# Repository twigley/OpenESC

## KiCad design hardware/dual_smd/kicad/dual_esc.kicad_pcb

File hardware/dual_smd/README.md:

# Dual-motor SMD ESC, AM32 version

Two independent 3-phase BLDC channels on one small board. Each channel has
its own Artery AT32F421 running the stock **AM32** firmware target
**`RR_ROBOT_DUAL_ESC_F421`** (hardware groups `AT_C` + `AT_045`), a TI
DRV8300 gate driver and three AOS AON7934 dual half-bridge MOSFETs. A shared
buck gives 5 V for the receiver (BEC), and an LDO gives 3.3 V for both MCUs.

**Status:** schematic drawn and checked (ERC clean). The PCB is **placed
but not routed**: 6 layers, 31 x 20 mm. It needs interactive routing in
KiCad (see [Routing notes](#routing-notes)). Not built. Part numbers marked
"verify" must be checked before ordering.

## Targets

| Item | Value |
|---|---|
| Battery | 2S Li-ion, 6.0 to 8.4 V |
| Current | about 10-12 A per motor, limit set in AM32 |
| Firmware | AM32, stock target `RR_ROBOT_DUAL_ESC_F421`, flashed on both MCUs; no `USE_INVERTED_*` |
| Board | 31 x 20 mm, 6-layer trial (L2 GND, L3/L4 signal, L5 VBAT), parts on both sides |
| Bulk caps | 4 x 220 uF 16 V on the battery leads (off-board, in the BOM) |

## Pin map (both channels, from AM32 `Inc/targets.h`)

| Function | AT32F421 pin (QFN32 no.) | Connects to |
|---|---|---|
| Phase A high / low | PA10 TMR1_CH3 (20) / PB1 TMR1_CH3N (15) | DRV8300 INHA (22) / INLA (1) |
| Phase B high / low | PA9 TMR1_CH2 (19) / PB0 TMR1_CH2N (14) | INHB (23) / INLB (2) |
| Phase C high / low | PA8 TMR1_CH1 (18) / PA7 TMR1_CH1N (13) | INHC (24) / INLC (3) |
| BEMF A / B / C | PA0 (6) / PA4 (10) / PA5 (11), comparator inverting inputs | 10k / 4.7k dividers from each phase |
| Neutral | PA1 (7), comparator non-inverting input | 3 x 10k from the phases, 1.5k to GND |
| Signal in | PA2 TMR15_CH1 (8) | 100 R to the SIG pad |
| Telemetry | PB6 USART1_TX (29) | TLM pad |
| Battery voltage | PA3 ADC3 (9) | 100k / 10k divider (shared by both MCUs) |
| Current | PA6 ADC6 (12) | INA186A1 via 1k / 10 nF |
| SWD | PA13 (23) / PA14 (24), NRST (4) | SWDIO / SWCLK / NRST pads, plus shared 3V3 / GND pads |
| BOOT0 | pin 31 | 10k to GND |

The pins were checked against the AT32F421 datasheet v2.02, Figure 4. The
AT32F421 QFN32 is **not** pin-identical to the STM32F051K8U: its pins 16 and
32 are PB2 and PB8, not VSS. Ground is the exposed pad only.

## Circuit notes

- **Gate driver:** DRV8300DRGER (VQFN-24), the D variant with internal
  bootstrap diodes. MODE is left open, so GLx follows INLx (non-inverted). DT
  is left open for the fixed 200 ns dead time, on top of AM32's DEAD_TIME 50.
  GVDD runs straight from VBAT (5-20 V) with 10 uF + 100 nF. Bootstrap caps
  are 100 nF 25 V. Source: TI SLVSFG5D Table 6-1 and section 9.2.2.
- **MOSFETs:** AON7934 has the high-side FET Q1 (D1 = VBAT) and the low-side
  FET Q2 (S2 = low-side source node) in one 3 x 3 mm package. The switch
  node is pad 9 (S1/D2). The footprint is made from AOS drawing PO-00136 rev
  C (DFN3x3A_8L_EP2) and is in `kicad/OpenESC_dual.pretty`. There are no
  gate series resistors, to save space. Each low-side gate has a 10k
  pull-down to GND. GND is the source potential plus the shunt's few mV.
- **Current sense:** each channel has one 0.5 mOhm low-side shunt from the
  three low-side sources to GND, feeding an INA186A1 (25 V/V). That gives
  12.5 mV/A against AM32's MILLIVOLT_PER_AMP 12, so readings are about 4 %
  high, trimmable in the configurator. REF is tied to GND (unidirectional).
- **BEMF:** 10k / 4.7k dividers (ratio 0.32, so 8.4 V gives 2.7 V). The
  virtual neutral is 3 x 10k with 1.5k to GND, the same ratio. There are no
  filter caps. The AM32 repository has firmware only, so there were no AM32
  reference values to compare against.
- **5 V BEC:** TPS62933 (3.8-30 V in, 3 A) at 1.2 MHz (RT to GND), with
  2.2 uH and 2 x 22 uF. The feedback divider is 31.6k / 10k for 5.0 V
  (TI SLUSEA4D Table 10-2). At 6.0 V in, the needed duty cycle is about 85 %,
  within the 98 % maximum.
- **3.3 V:** TLV75533PDBV from 5 V, with 1 uF in and out.
- **Heat:** RDS(on) at 4.5 V is 11.6-15.8 mOhm max per FET, and a 2S pack
  gives only 6-8 V of gate drive. At 12 A that is about 1.7-2.3 W in the
  conducting pair. Expect airflow to be needed above about 8 A continuous.

## Flashing AM32

1. With the battery disconnected, power the board from a 3.3 V SWD
   programmer through the 3V3 / GND pads. Connect SWDIO, SWCLK and NRST for
   the channel being flashed. Flash the AM32 bootloader built for the F421
   with its input on PA2 (from the AM32 bootloader releases; check the file
   name there) using an SWD probe that supports the AT32F421, such as
   Artery's AT-Link or an ST-Link with OpenOCD's AT32 support. Repeat for
   the second MCU.
2. Connect the battery and the signal wires. With the AM32 configurator
   (web or desktop), through a betaflight passthrough or a USB-serial
   one-wire adapter on each SIG pad, flash `RR_ROBOT_DUAL_ESC_F421` to each
   channel and set the current limit (10-12 A), motor direction and timing.
3. After that, firmware updates go over the signal wire. SWD is needed
   only once.

## PCB status

**Placed, not routed.** The board is 31 x 20 mm with 6 layers. All 129
on-board parts fit with no courtyard overlaps, and placement DRC is clean
(only unconnected items). Renders: `kicad/render_top.png`,
`kicad/render_bottom.png`.

### Stackup (1.6 mm, JLC 6-layer style)

| Layer | Use |
|---|---|
| L1 top (1 oz) | MOSFETs, phase / battery pads, shunts, gate resistors, BEC, LDO; power zones (phase nodes, low-side source buses, VBAT drain islands) |
| L2 | Solid GND plane |
| L3, L4 | Signal |
| L5 | VBAT plane (GND beyond x = 27.4 mm) |
| L6 bottom (1 oz) | Both DRV8300s, both MCUs, current-sense amps, BEMF networks, small passives |

**Outer copper is 1 oz.** JLC offers 2 oz outer on 6-layer boards, but then
the minimum trace / space is 0.16 mm, and the QFN escapes need 0.13 mm.
At 1 oz the outer power zones carry about half the current of 2 oz, so the
10-12 A phase and battery paths should be widened where possible,
solder-tinned, or reinforced with bus wire. The MOSFET drains also reach the
L5 VBAT plane through vias.

**Via-in-pad:** every DRV8300 and MCU signal pin has a filled via-in-pad,
0.3 mm diameter with a 0.15 mm hole, epoxy filled and capped. That is within
JLC's multilayer minimum of a 0.15 mm hole / 0.25 mm via, at a surcharge.
One JLC blog gives 0.20 mm as the minimum hole for via-in-pad, so confirm
before ordering. A 0.20 mm hole means 0.35-0.4 mm vias, which do not fit
side by side at the MCU's 0.4 mm pitch. The vias are staggered along the
pad length.

**Placement:**
- Both DRV8300s are in the bottom middle band, with only the low-side bus
  zones above them. Bootstrap caps sit between the drivers, GVDD caps beside
  them.
- The 4.7 R gate series resistors are on top, just under each gate pin.
- The BEMF networks, BEMF filter caps and gate pull-downs are on the bottom,
  under the phase pads.
- The MCUs are bottom right with nothing above their pins (checked with
  `tools/above_check.py`).
- The bus caps are under the phase pads. The LDO, BEC and SWD pads are top
  right.

**0201 parts:** 48 small-signal parts are 0201. LCSC stock was checked
2026-11-21:
- 100 nF 10 V: C284966
- 10 nF 25 V: C285010
- 1 nF 50 V: C301887
- 10k: C6853700
- Other resistor values: UNI-ROYAL 0201WMF ±1 % series

### Routing notes

Automated routing was tried and plateaued at about 55-65 conflicting nets
in every setup: Freerouting 2.5.0, and `tools/gridroute.py` / `negroute.py`
on 4 and 6 layers, with and without via-in-pad. Route it interactively in
KiCad:

1. Route the DRV8300 and MCU fanouts first. Drop each signal pin through
   its via-in-pad to L3 / L4, then run the six INH/INL lines per channel,
   the gate lines (driver -> 4.7 R on top -> FET gate) and the BST / SH
   lines on L3 / L4.
2. Keep each GHx / SHx pair together. Keep gate loops short.
3. Power stays in the L1 / L6 zones: phase nodes, low-side buses to the
   shunts, and VBAT drain islands with their vias to L5. Don't route
   signals through them on L1.
4. Run the BEMF / neutral / ISENSE lines to the MCU on L3 / L4. The shunt
   Kelvin lead (INA186 IN+) goes from the LS tap via.
5. Finish with the top / bottom GND fill and stitching vias to L2. GND /
   VBAT pads already have fanout vias where `tools/route_pcb.py` placed
   them.

## Files

- `tools/gen_schematic.py`: the netlist (`PARTS`), the single source of
  truth. Running it writes `BOM.csv` and redraws the schematic.
- `tools/draw_schematic.py`: draws `kicad/dual_esc.kicad_sch` as a wired,
  readable sheet. Labels are used only between blocks.
- `tools/check_schematic.py`: rebuilds connectivity from the drawn wires and
  fails unless it matches `PARTS`.
- `tools/above_check.py`: checks no part on the other side sits over a DRV8300 / MCU pin.
- `tools/negroute.py`: negotiated-congestion (rip-up) router experiment.
- `tools/gridroute.py`: grid maze router for the outer layers (power fanout, then signal nets).
- `tools/route_pcb.py`: power fanout, Freerouting run, keep-out removal, GND fill and stitching.
- `tools/build_pcb.py`: builds `kicad/dual_esc.kicad_pcb`. It places the parts,
  draws the power copper as zones, and links each footprint to its schematic
  symbol so the GUI's Update PCB keeps working. Run it with KiCad's Python.

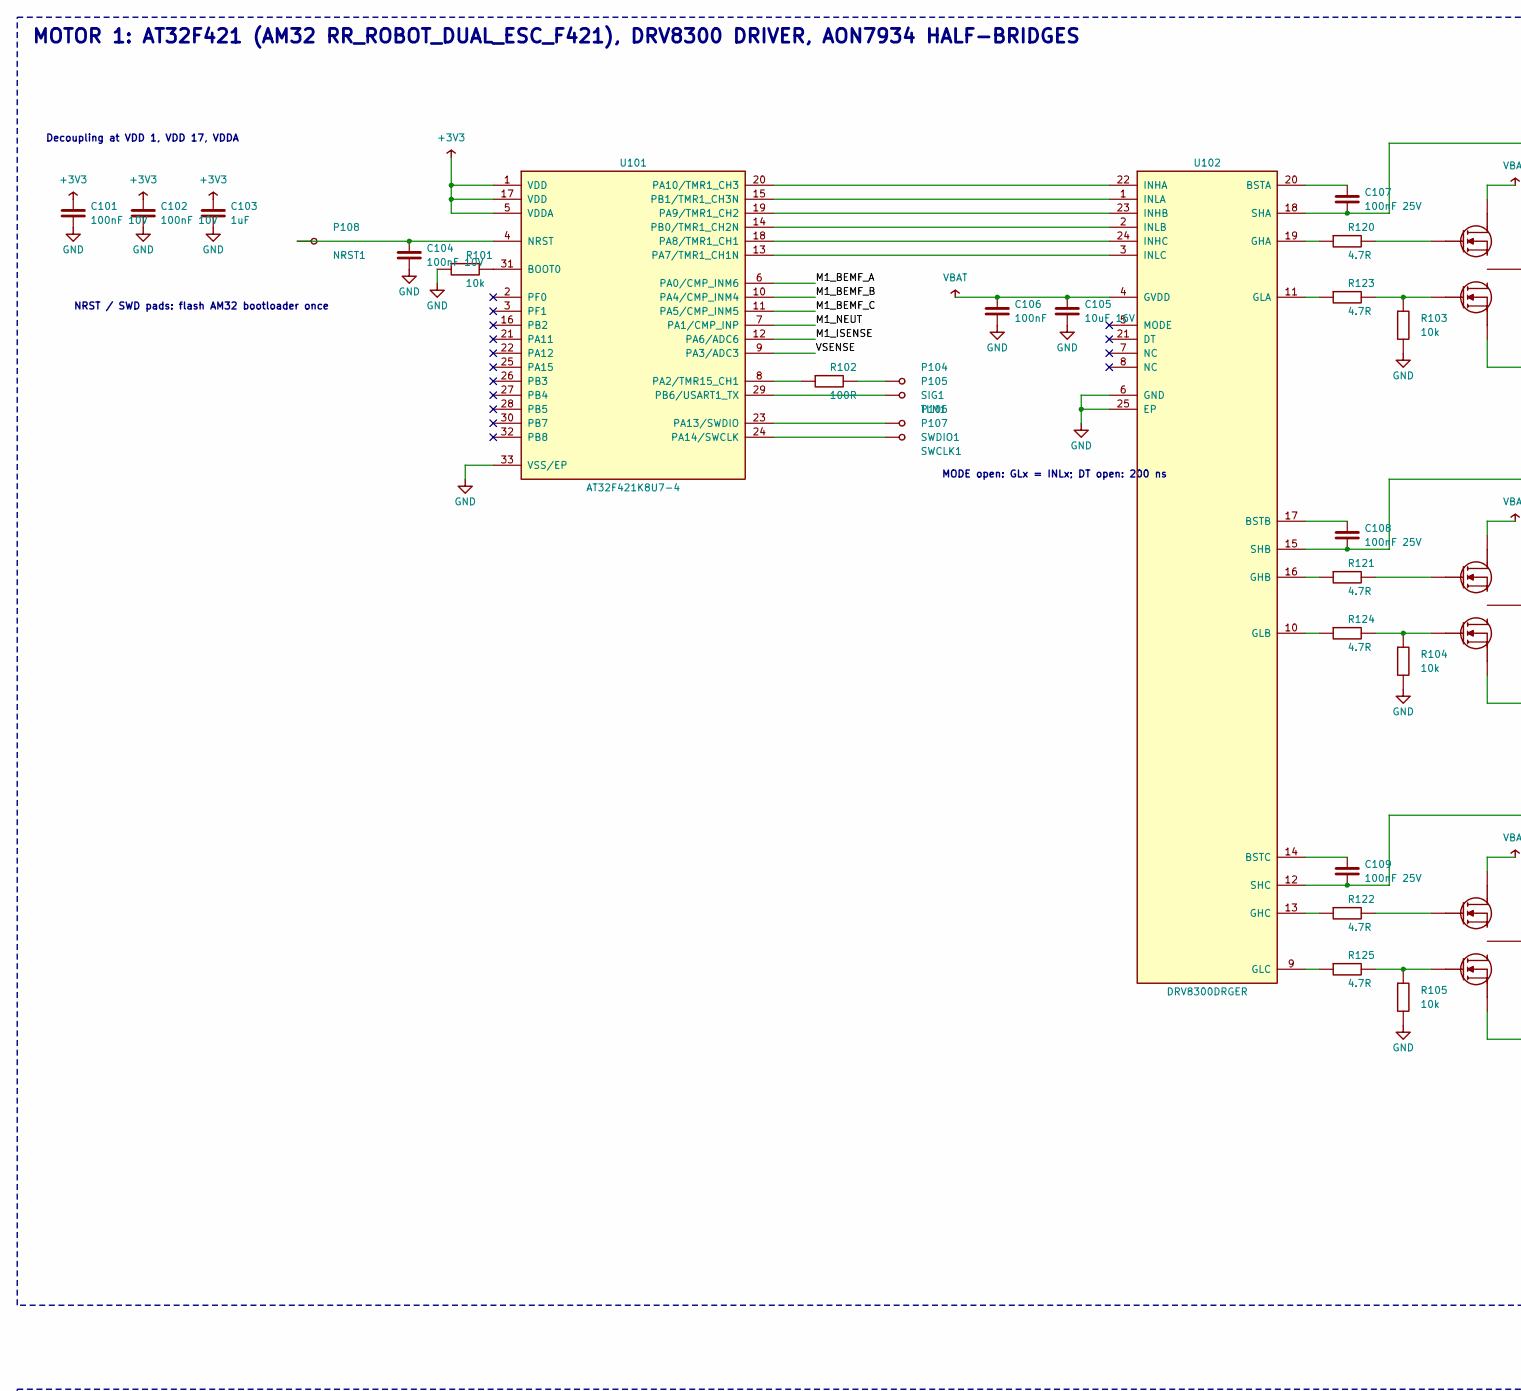
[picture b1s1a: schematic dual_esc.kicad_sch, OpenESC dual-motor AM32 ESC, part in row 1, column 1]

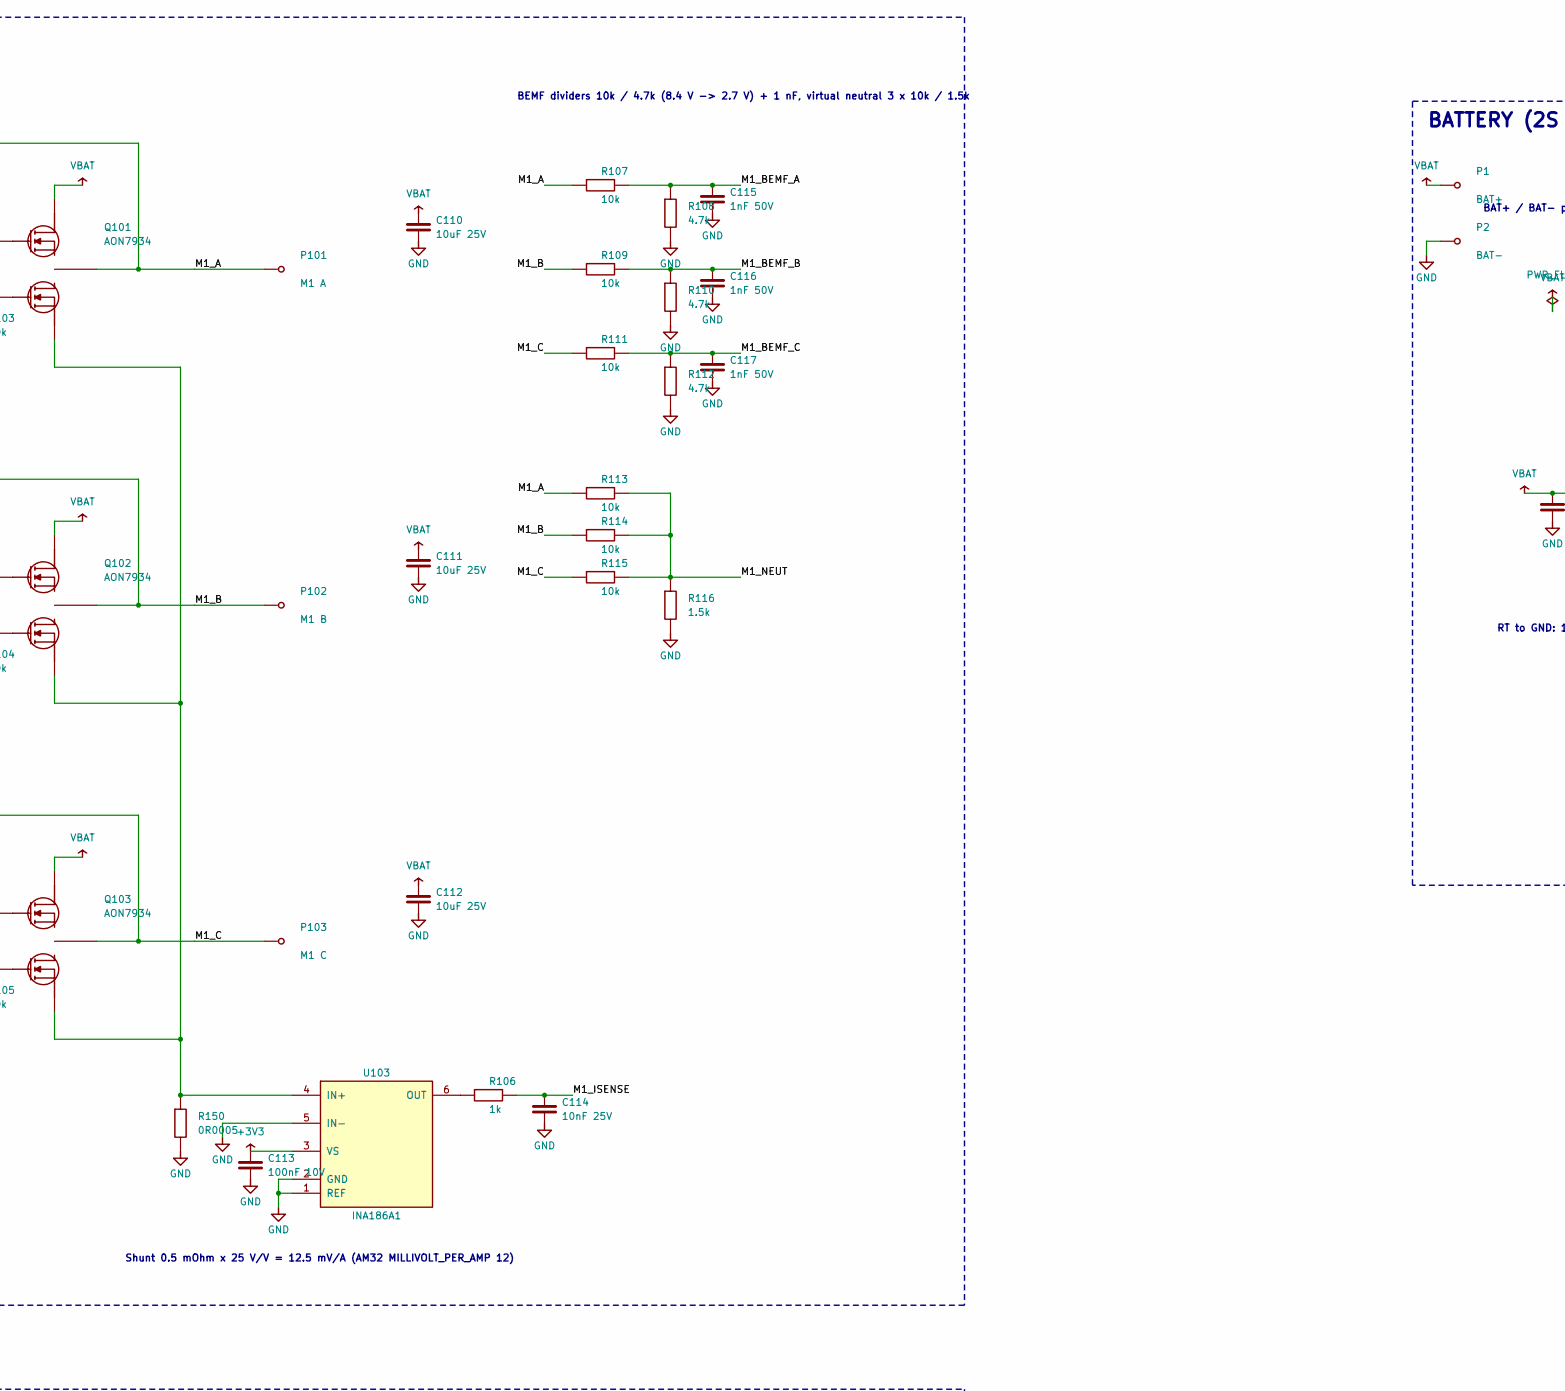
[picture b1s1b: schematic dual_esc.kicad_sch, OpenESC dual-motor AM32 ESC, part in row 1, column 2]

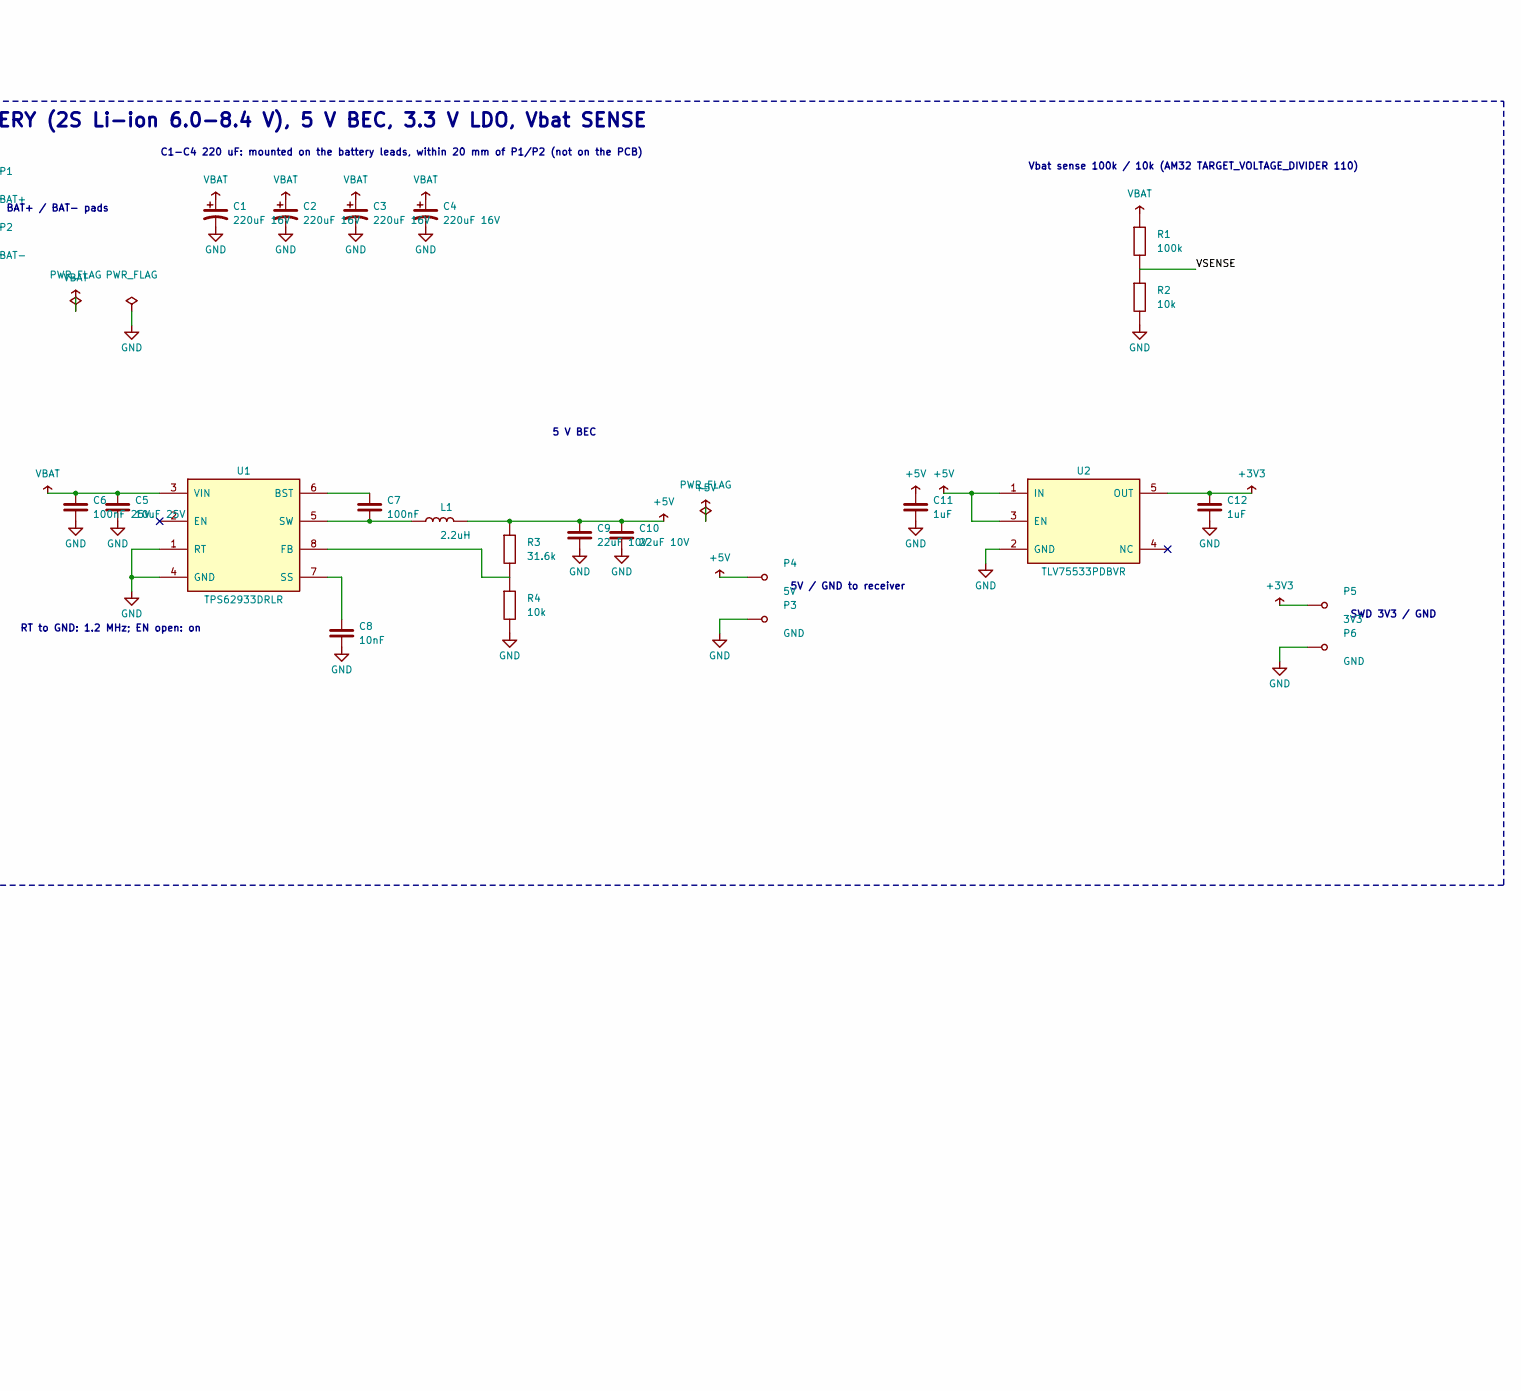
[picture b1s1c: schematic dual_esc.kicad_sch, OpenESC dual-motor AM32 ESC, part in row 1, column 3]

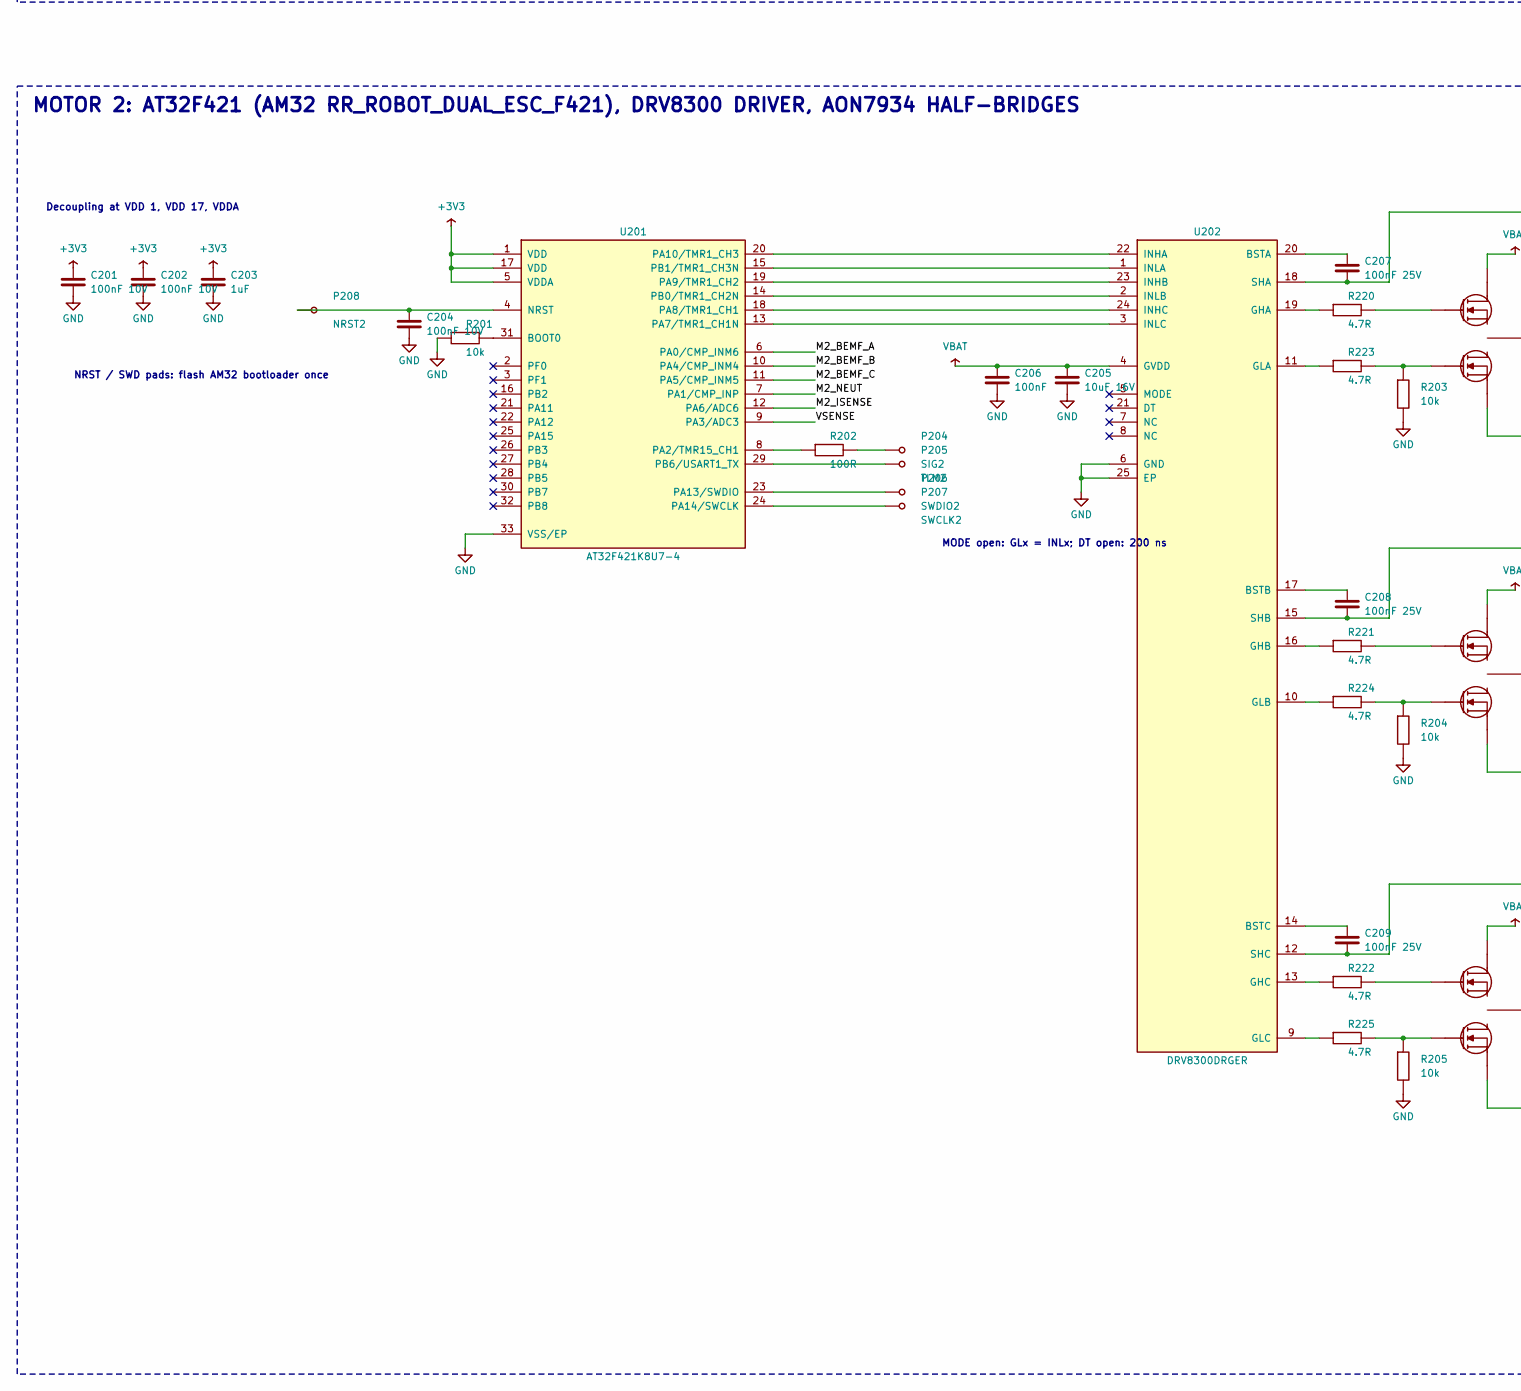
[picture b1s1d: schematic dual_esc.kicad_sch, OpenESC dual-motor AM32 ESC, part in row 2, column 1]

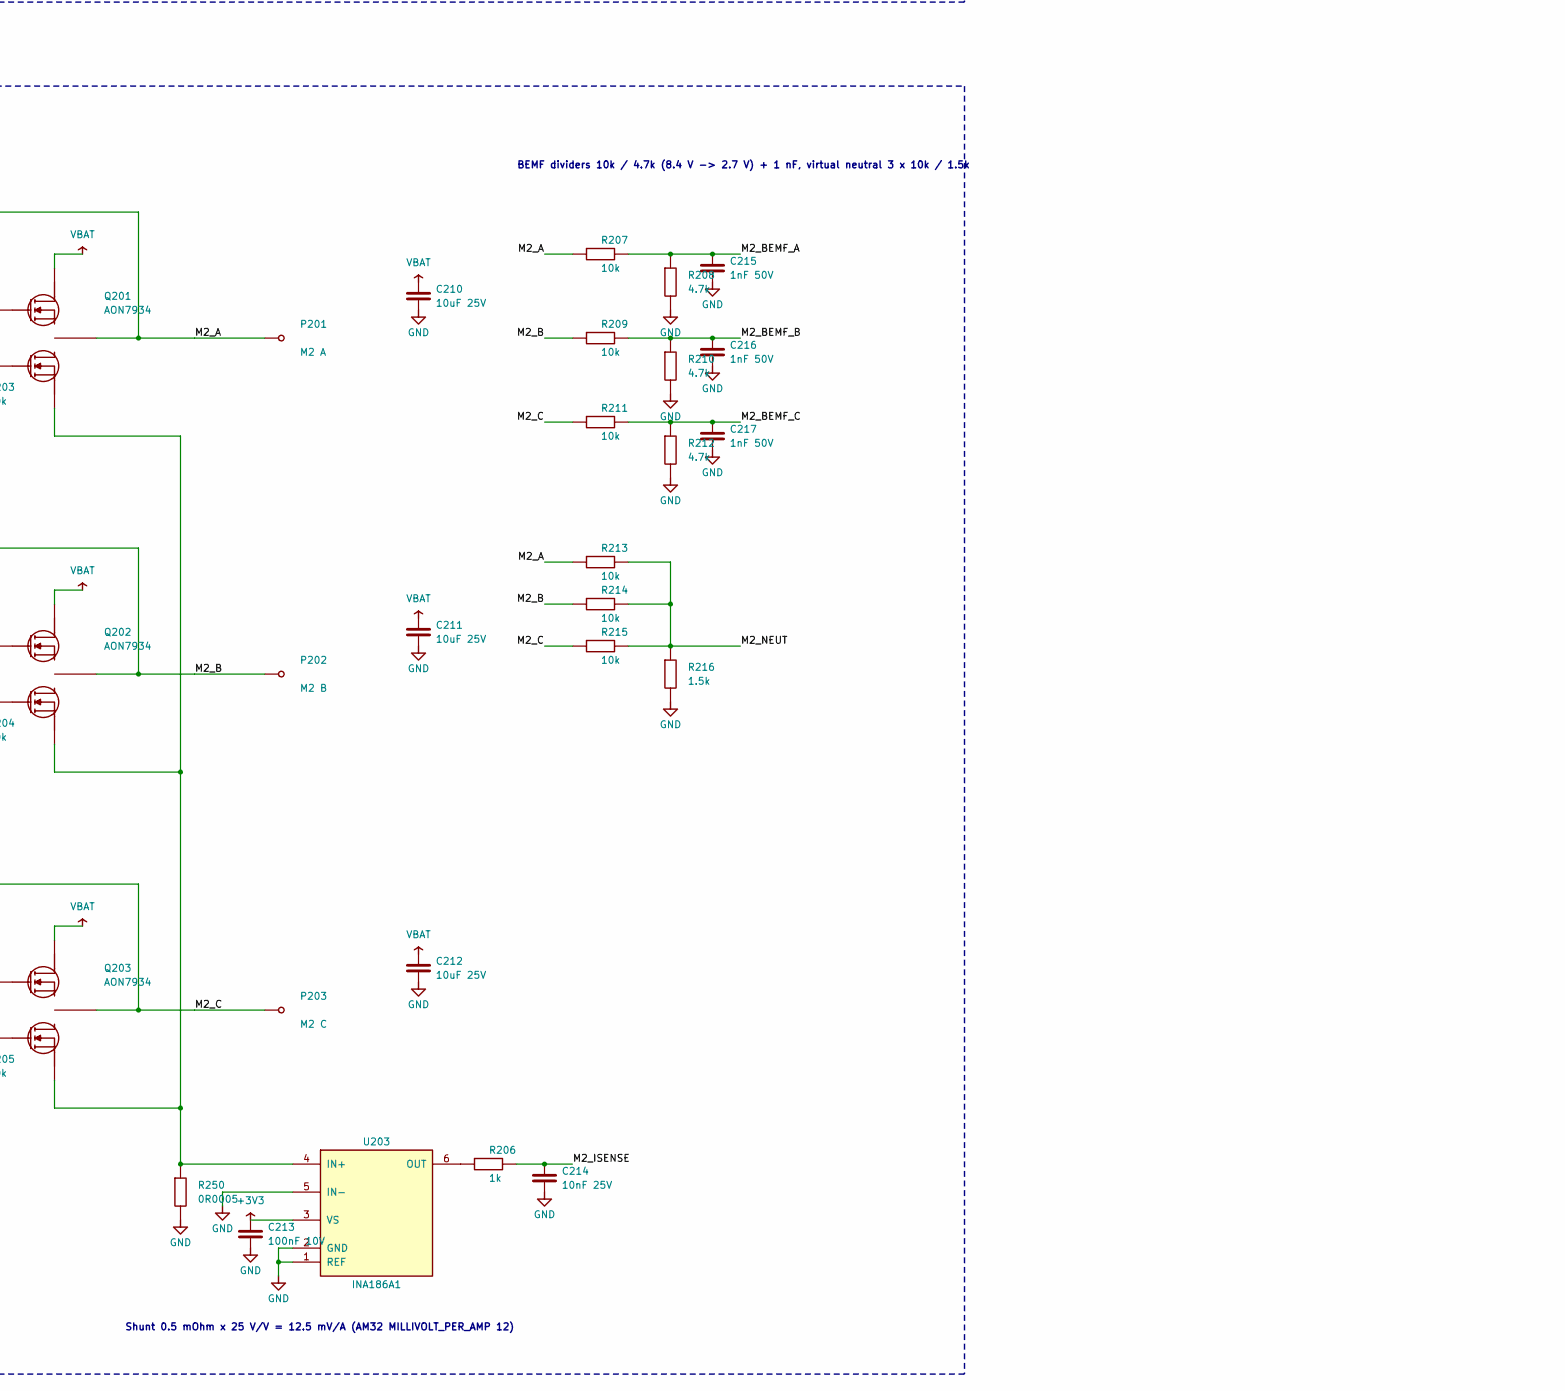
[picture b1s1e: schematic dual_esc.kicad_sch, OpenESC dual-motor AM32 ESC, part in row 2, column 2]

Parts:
C1, C2, C3, C4: 220uF 16V; CP_Elec_6.3x7.7; MPN low-ESR polymer/electrolytic, on batter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
C5, C110, C111, C112, C210, C211, C212: 10uF 25V; C_0805_2012Metric
C6, C107, C108, C109, C207, C208, C209: 100nF 25V; C_0402_1005Metric
C7, C106, C206: 100nF; C_0402_1005Metric
C8: 10nF; C_0402_1005Metric
C9, C10: 22uF 10V; C_0603_1608Metric
C11, C12, C103, C203: 1uF; C_0402_1005Metric
C101, C102, C104, C113, C201, C202, C204, C213: 100nF 10V; C_0201_0603Metric
C105, C205: 10uF 16V; C_0603_1608Metric
C114, C214: 10nF 25V; C_0201_0603Metric
C115, C116, C117, C215, C216, C217: 1nF 50V; C_0201_0603Metric
L1: 2.2uH; L_Changjiang_FNR3015S; MPN Changjiang FNR3015S2R2MT, 3x3 mm (verif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
P1: BAT+; Pad_SMD_2.5x5.0mm
P2: BAT-; Pad_SMD_2.5x5.0mm
P3: GND; Pad_SMD_1.5x1.5mm_Tight
P4: 5V; Pad_SMD_1.5x1.5mm_Tight
P5: 3V3; Pad_SMD_1.0x1.0mm_Tight
P6: GND; Pad_SMD_1.0x1.0mm_Tight
P101: M1 A; Pad_SMD_2.5x3.0mm
P102: M1 B; Pad_SMD_2.5x3.0mm
P103: M1 C; Pad_SMD_2.5x3.0mm
P104: SIG1; Pad_SMD_1.5x1.5mm_Tight
P105: TLM1; Pad_SMD_1.0x1.0mm_Tight
P106: SWDIO1; Pad_SMD_1.0x1.0mm_Tight
P107: SWCLK1; Pad_SMD_1.0x1.0mm_Tight
P108: NRST1; Pad_SMD_1.0x1.0mm_Tight
P201: M2 A; Pad_SMD_2.5x3.0mm
P202: M2 B; Pad_SMD_2.5x3.0mm
P203: M2 C; Pad_SMD_2.5x3.0mm
P204: SIG2; Pad_SMD_1.5x1.5mm_Tight
P205: TLM2; Pad_SMD_1.0x1.0mm_Tight
P206: SWDIO2; Pad_SMD_1.0x1.0mm_Tight
P207: SWCLK2; Pad_SMD_1.0x1.0mm_Tight
P208: NRST2; Pad_SMD_1.0x1.0mm_Tight
Q101, Q102, Q103, Q201, Q202, Q203: AON7934; AOS_DFN3x3A-8L-EP2_3x3mm_P0.65mm; MPN AON7934
R1: 100k; R_0201_0603Metric
R2, R101, R103, R104, R105, R107, R109, R111, R113, R114, R115, R201, R203, R204, R205, R207, R209, R211, R213, R214, R215: 10k; R_0201_0603Metric
R3: 31.6k; R_0402_1005Metric
R4: 10k; R_0402_1005Metric
R102, R202: 100R; R_0201_0603Metric
R106, R206: 1k; R_0201_0603Metric
R108, R110, R112, R208, R210, R212: 4.7k; R_0201_0603Metric
R116, R216: 1.5k; R_0201_0603Metric
R120, R121, R122, R123, R124, R125, R220, R221, R222, R223, R224, R225: 4.7R; R_0201_0603Metric
R150, R250: 0R0005; R_1206_3216Metric; MPN e.g. WSLP1206R0005 (verify)
U1: TPS62933DRLR; SOT-583-8; MPN TPS62933DRLR
U2: TLV75533PDBVR; SOT-23-5; MPN TLV75533PDBVR
U101, U201: AT32F421K8U7-4; QFN-32-1EP_4x4mm_P0.4mm_EP2.65x2.65mm; MPN AT32F421K8U7-4
U102, U202: DRV8300DRGER; VQFN-24-1EP_4x4mm_P0.5mm_EP2.45x2.45mm; MPN DRV8300DRGER
U103, U203: INA186A1; SOT-363_SC-70-6; MPN INA186A1IDCKR

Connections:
+3V3: C12.1, C101.1, C102.1, C103.1, C113.1, C201.1, C202.1, C203.1, C213.1, P5.1, U2.5 (OUT), U101.1 (VDD), U101.5 (VDDA), U101.17 (VDD), U103.3 (VS), U201.1 (VDD), U201.5 (VDDA), U201.17 (VDD), U203.3 (VS)
+5V: C9.1, C10.1, C11.1, L1.2, P4.1, R3.1, U2.1 (IN), U2.3 (EN)
BEC_BST: C7.1, U1.6 (BST)
BEC_FB: R3.2, R4.1, U1.8 (FB)
BEC_SS: C8.1, U1.7 (SS)
BEC_SW: C7.2, L1.1, U1.5 (SW)
GND: C1.2, C2.2, C3.2, C4.2, C5.2, C6.2, C8.2, C9.2, C10.2, C11.2, C12.2, C101.2, C102.2, C103.2, C104.2, C105.2, C106.2, C110.2, C111.2, C112.2, C113.2, C114.2, C115.2, C116.2, C117.2, C201.2, C202.2, C203.2, C204.2, C205.2, C206.2, C210.2, C211.2, C212.2, C213.2, C214.2, C215.2, C216.2, C217.2, P2.1, P3.1, P6.1, R2.2, R4.2, R101.1, R103.2, R104.2, R105.2, R108.2, R110.2, R112.2, R116.2, R150.2, R201.1, R203.2, R204.2, R205.2, R208.2, R210.2, R212.2, R216.2, R250.2, U1.1 (RT), U1.4 (GND), U2.2 (GND), U101.33 (VSS/EP), U102.6 (GND), U102.25 (EP), U103.1 (REF), U103.2 (GND), U103.5 (IN-), U201.33 (VSS/EP), U202.6 (GND), U202.25 (EP), U203.1 (REF), U203.2 (GND), U203.5 (IN-)
M1_A: C107.2, P101.1, Q101.9 (S1/D2), R107.1, R113.1, U102.18 (SHA)
M1_B: C108.2, P102.1, Q102.9 (S1/D2), R109.1, R114.1, U102.15 (SHB)
M1_BEMF_A: C115.1, R107.2, R108.1, U101.6 (PA0/CMP_INM6)
M1_BEMF_B: C116.1, R109.2, R110.1, U101.10 (PA4/CMP_INM4)
M1_BEMF_C: C117.1, R111.2, R112.1, U101.11 (PA5/CMP_INM5)
M1_BOOT0: R101.2, U101.31 (BOOT0)
M1_BSTA: C107.1, U102.20 (BSTA)
M1_BSTB: C108.1, U102.17 (BSTB)
M1_BSTC: C109.1, U102.14 (BSTC)
M1_C: C109.2, P103.1, Q103.9 (S1/D2), R111.1, R115.1, U102.12 (SHC)
M1_GHA: Q101.1 (G1), R120.2
M1_GHA_D: R120.1, U102.19 (GHA)
M1_GHB: Q102.1 (G1), R121.2
M1_GHB_D: R121.1, U102.16 (GHB)
M1_GHC: Q103.1 (G1), R122.2
M1_GHC_D: R122.1, U102.13 (GHC)
M1_GLA: Q101.8 (G2), R103.1, R123.2
M1_GLA_D: R123.1, U102.11 (GLA)
M1_GLB: Q102.8 (G2), R104.1, R124.2
M1_GLB_D: R124.1, U102.10 (GLB)
M1_GLC: Q103.8 (G2), R105.1, R125.2
M1_GLC_D: R125.1, U102.9 (GLC)
M1_INHA: U101.20 (PA10/TMR1_CH3), U102.22 (INHA)
M1_INHB: U101.19 (PA9/TMR1_CH2), U102.23 (INHB)
M1_INHC: U101.18 (PA8/TMR1_CH1), U102.24 (INHC)
M1_INLA: U101.15 (PB1/TMR1_CH3N), U102.1 (INLA)
M1_INLB: U101.14 (PB0/TMR1_CH2N), U102.2 (INLB)
M1_INLC: U101.13 (PA7/TMR1_CH1N), U102.3 (INLC)
M1_IOUT: R106.1, U103.6 (OUT)
M1_ISENSE: C114.1, R106.2, U101.12 (PA6/ADC6)
M1_LS: Q101.5 (S2), Q101.6 (S2), Q101.7 (S2), Q102.5 (S2), Q102.6 (S2), Q102.7 (S2), Q103.5 (S2), Q103.6 (S2), Q103.7 (S2), R150.1, U103.4 (IN+)
M1_NEUT: R113.2, R114.2, R115.2, R116.1, U101.7 (PA1/CMP_INP)
M1_NRST: C104.1, P108.1, U101.4 (NRST)
M1_SIG: R102.1, U101.8 (PA2/TMR15_CH1)
M1_SIG_IN: P104.1, R102.2
M1_SWCLK: P107.1, U101.24 (PA14/SWCLK)
M1_SWDIO: P106.1, U101.23 (PA13/SWDIO)
M1_TLM: P105.1, U101.29 (PB6/USART1_TX)
M2_A: C207.2, P201.1, Q201.9 (S1/D2), R207.1, R213.1, U202.18 (SHA)
M2_B: C208.2, P202.1, Q202.9 (S1/D2), R209.1, R214.1, U202.15 (SHB)
M2_BEMF_A: C215.1, R207.2, R208.1, U201.6 (PA0/CMP_INM6)
M2_BEMF_B: C216.1, R209.2, R210.1, U201.10 (PA4/CMP_INM4)
M2_BEMF_C: C217.1, R211.2, R212.1, U201.11 (PA5/CMP_INM5)
M2_BOOT0: R201.2, U201.31 (BOOT0)
M2_BSTA: C207.1, U202.20 (BSTA)
M2_BSTB: C208.1, U202.17 (BSTB)
M2_BSTC: C209.1, U202.14 (BSTC)
M2_C: C209.2, P203.1, Q203.9 (S1/D2), R211.1, R215.1, U202.12 (SHC)
M2_GHA: Q201.1 (G1), R220.2
M2_GHA_D: R220.1, U202.19 (GHA)
M2_GHB: Q202.1 (G1), R221.2
M2_GHB_D: R221.1, U202.16 (GHB)
M2_GHC: Q203.1 (G1), R222.2
M2_GHC_D: R222.1, U202.13 (GHC)
M2_GLA: Q201.8 (G2), R203.1, R223.2
M2_GLA_D: R223.1, U202.11 (GLA)
M2_GLB: Q202.8 (G2), R204.1, R224.2
M2_GLB_D: R224.1, U202.10 (GLB)
M2_GLC: Q203.8 (G2), R205.1, R225.2
M2_GLC_D: R225.1, U202.9 (GLC)
M2_INHA: U201.20 (PA10/TMR1_CH3), U202.22 (INHA)
M2_INHB: U201.19 (PA9/TMR1_CH2), U202.23 (INHB)
M2_INHC: U201.18 (PA8/TMR1_CH1), U202.24 (INHC)
M2_INLA: U201.15 (PB1/TMR1_CH3N), U202.1 (INLA)
M2_INLB: U201.14 (PB0/TMR1_CH2N), U202.2 (INLB)
M2_INLC: U201.13 (PA7/TMR1_CH1N), U202.3 (INLC)
M2_IOUT: R206.1, U203.6 (OUT)
M2_ISENSE: C214.1, R206.2, U201.12 (PA6/ADC6)
M2_LS: Q201.5 (S2), Q201.6 (S2), Q201.7 (S2), Q202.5 (S2), Q202.6 (S2), Q202.7 (S2), Q203.5 (S2), Q203.6 (S2), Q203.7 (S2), R250.1, U203.4 (IN+)
M2_NEUT: R213.2, R214.2, R215.2, R216.1, U201.7 (PA1/CMP_INP)
M2_NRST: C204.1, P208.1, U201.4 (NRST)
M2_SIG: R202.1, U201.8 (PA2/TMR15_CH1)
M2_SIG_IN: P204.1, R202.2
M2_SWCLK: P207.1, U201.24 (PA14/SWCLK)
M2_SWDIO: P206.1, U201.23 (PA13/SWDIO)
M2_TLM: P205.1, U201.29 (PB6/USART1_TX)
VBAT: C1.1, C2.1, C3.1, C4.1, C5.1, C6.1, C105.1, C106.1, C110.1, C111.1, C112.1, C205.1, C206.1, C210.1, C211.1, C212.1, P1.1, Q101.2 (D1), Q101.3 (D1), Q101.4 (D1), Q101.10 (D1), Q102.2 (D1), Q102.3 (D1), Q102.4 (D1), Q102.10 (D1), Q103.2 (D1), Q103.3 (D1), Q103.4 (D1), Q103.10 (D1), Q201.2 (D1), Q201.3 (D1), Q201.4 (D1), Q201.10 (D1), Q202.2 (D1), Q202.3 (D1), Q202.4 (D1), Q202.10 (D1), Q203.2 (D1), Q203.3 (D1), Q203.4 (D1), Q203.10 (D1), R1.1, U1.3 (VIN), U102.4 (GVDD), U202.4 (GVDD)
VSENSE: R1.2, R2.1, U101.9 (PA3/ADC3), U201.9 (PA3/ADC3)

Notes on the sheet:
MOTOR 1: AT32F421 (AM32 RR_ROBOT_DUAL_ESC_F421), DRV8300 DRIVER, AON7934 HALF-BRIDGES
Decoupling at VDD 1, VDD 17, VDDA
NRST / SWD pads: flash AM32 bootloader once
MODE open: GLx = INLx; DT open: 200 ns
Shunt 0.5 mOhm x 25 V/V = 12.5 mV/A (AM32 MILLIVOLT_PER_AMP 12)
BEMF dividers 10k / 4.7k (8.4 V -> 2.7 V) + 1 nF, virtual neutral 3 x 10k / 1.5k
MOTOR 2: AT32F421 (AM32 RR_ROBOT_DUAL_ESC_F421), DRV8300 DRIVER, AON7934 HALF-BRIDGES
BATTERY (2S Li-ion 6.0-8.4 V), 5 V BEC, 3.3 V LDO, Vbat SENSE
BAT+ / BAT- pads
C1-C4 220 uF: mounted on the battery leads, within 20 mm of P1/P2 (not on the PCB)
Vbat sense 100k / 10k (AM32 TARGET_VOLTAGE_DIVIDER 110)
RT to GND: 1.2 MHz; EN open: on
5 V BEC
5V / GND to receiver
SWD 3V3 / GND

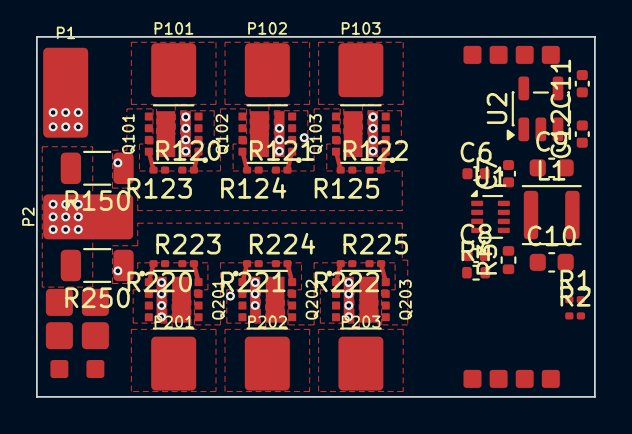
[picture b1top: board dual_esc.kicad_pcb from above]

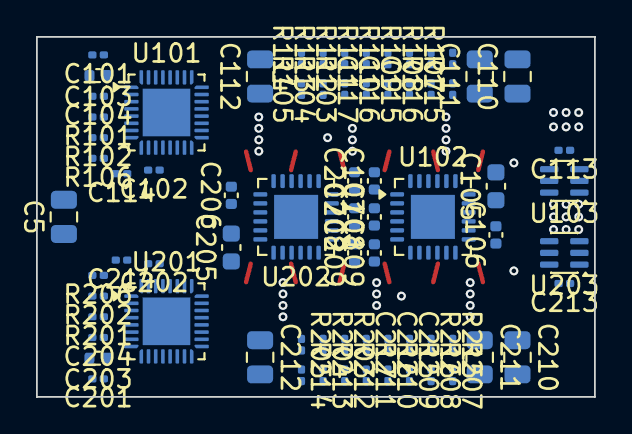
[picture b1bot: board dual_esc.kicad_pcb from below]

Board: 6 copper layers, 31.0 x 20.0 mm, 129 parts (73 on the bottom side), 85 nets.

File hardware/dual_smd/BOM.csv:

Refs,Qty,Value,Part number,Footprint,Notes
U101 U201,2,AT32F421K8U7-4,AT32F421K8U7-4,QFN-32-1EP_4x4mm_P0.4mm_EP2.65x2.65mm,"AM32 target RR_ROBOT_DUAL_ESC_F421; 4x4 mm QFN32 (K8U7 = 5x5 mm, same pinout) chosen to fit 28 x 20 mm"
U102 U202,2,DRV8300DRGER,DRV8300DRGER,VQFN-24-1EP_4x4mm_P0.5mm_EP2.45x2.45mm,"D = internal bootstrap diodes; MODE and DT open (non-inverted INLx, 200 ns dead time); GVDD 5-20 V"
C101 C102 C104 C113 C201 C202 C204 C213,8,100nF 10V,generic,C_0201_0603Metric,
C103 C203 C11 C12,4,1uF,generic,C_0402_1005Metric,
R101 R103 R104 R105 R107 R109 R111 R113 R114 R115 R201 R203 R204 R205 R207 R209 R211 R213 R214 R215 R2,21,10k,generic,R_0201_0603Metric,
R102 R202,2,100R,generic,R_0201_0603Metric,
C105 C205,2,10uF 16V,generic,C_0603_1608Metric,
C106 C206 C7,3,100nF,generic,C_0402_1005Metric,
C107 C108 C109 C207 C208 C209 C6,7,100nF 25V,generic,C_0402_1005Metric,
Q101 Q102 Q103 Q201 Q202 Q203,6,AON7934,AON7934,AOS_DFN3x3A-8L-EP2_3x3mm_P0.65mm,"30 V dual asymmetric half-bridge, DFN 3x3A; RDS(on) at 4.5 V: 15.8 mOhm (Q1) / 11.6 mOhm (Q2) max"
R120 R123 R121 R124 R122 R125 R220 R223 R221 R224 R222 R225,12,4.7R,generic,R_0201_0603Metric,
C110 C111 C112 C210 C211 C212 C5,7,10uF 25V,generic,C_0805_2012Metric,
R150 R250,2,0R0005,e.g. WSLP1206R0005 (verify),R_1206_3216Metric,
U103 U203,2,INA186A1,INA186A1IDCKR,SOT-363_SC-70-6,25 V/V; 0.5 mOhm shunt gives 12.5 mV/A (AM32 MILLIVOLT_PER_AMP 12)
R106 R206,2,1k,generic,R_0201_0603Metric,
C114 C214,2,10nF 25V,generic,C_0201_0603Metric,
R108 R110 R112 R208 R210 R212,6,4.7k,generic,R_0201_0603Metric,
R116 R216,2,1.5k,generic,R_0201_0603Metric,
C115 C116 C117 C215 C216 C217,6,1nF 50V,generic,C_0201_0603Metric,
P101,1,M1 A,generic,Pad_SMD_2.5x3.0mm,
P102,1,M1 B,generic,Pad_SMD_2.5x3.0mm,
P103,1,M1 C,generic,Pad_SMD_2.5x3.0mm,
P104,1,SIG1,generic,Pad_SMD_1.5x1.5mm_Tight,
P105,1,TLM1,generic,Pad_SMD_1.0x1.0mm_Tight,
P106,1,SWDIO1,generic,Pad_SMD_1.0x1.0mm_Tight,
P107,1,SWCLK1,generic,Pad_SMD_1.0x1.0mm_Tight,
P108,1,NRST1,generic,Pad_SMD_1.0x1.0mm_Tight,
P201,1,M2 A,generic,Pad_SMD_2.5x3.0mm,
P202,1,M2 B,generic,Pad_SMD_2.5x3.0mm,
P203,1,M2 C,generic,Pad_SMD_2.5x3.0mm,
P204,1,SIG2,generic,Pad_SMD_1.5x1.5mm_Tight,
P205,1,TLM2,generic,Pad_SMD_1.0x1.0mm_Tight,
P206,1,SWDIO2,generic,Pad_SMD_1.0x1.0mm_Tight,
P207,1,SWCLK2,generic,Pad_SMD_1.0x1.0mm_Tight,
P208,1,NRST2,generic,Pad_SMD_1.0x1.0mm_Tight,
P1,1,BAT+,generic,Pad_SMD_2.5x5.0mm,
P2,1,BAT-,generic,Pad_SMD_2.5x5.0mm,
P3,1,GND,generic,Pad_SMD_1.5x1.5mm_Tight,
P4,1,5V,generic,Pad_SMD_1.5x1.5mm_Tight,
P5,1,3V3,generic,Pad_SMD_1.0x1.0mm_Tight,
P6,1,GND,generic,Pad_SMD_1.0x1.0mm_Tight,
C1 C2 C3 C4,4,220uF 16V,"low-ESR polymer/electrolytic, on battery leads",CP_Elec_6.3x7.7,OFF-BOARD: solder across the battery leads within 20 mm of BAT+/BAT-.
R1,1,100k,generic,R_0201_0603Metric,
U1,1,TPS62933DRLR,TPS62933DRLR,SOT-583-8,"3.8-30 V in, 3 A; 1.2 MHz (RT to GND); 5 V BEC for the receiver"
C8,1,10nF,generic,C_0402_1005Metric,
L1,1,2.2uH,"Changjiang FNR3015S2R2MT, 3x3 mm (verify Isat >= 2.5 A)",L_Changjiang_FNR3015S,
R3,1,31.6k,generic,R_0402_1005Metric,
R4,1,10k,generic,R_0402_1005Metric,
C9 C10,2,22uF 10V,generic,C_0603_1608Metric,
U2,1,TLV75533PDBVR,TLV75533PDBVR,SOT-23-5,"3.3 V for both MCUs, from +5V"

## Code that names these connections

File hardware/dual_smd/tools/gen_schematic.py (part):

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
# --------------------------------------------------------------- per motor
# AM32 RR_ROBOT_DUAL_ESC_F421 = HARDWARE_GROUP_AT_C + AT_045:
#   A: INH PA10 (TMR1_CH3)  INL PB1 (CH3N)   BEMF PA0
#   B: INH PA9  (CH2)       INL PB0 (CH2N)   BEMF PA4
#   C: INH PA8  (CH1)       INL PA7 (CH1N)   BEMF PA5
#   neutral PA1 (comparator +), signal in PA2 (TMR15_CH1), telemetry PB6
#   (USART1_TX), Vbat sense PA3 (ADC3), current sense PA6 (ADC6).
MCU_PINS = {"1": "+3V3", "2": None, "3": None, "4": "NRST", "5": "+3V3",
            "6": "BEMF_A", "7": "NEUT", "8": "SIG", "9": "VSENSE", "10": "BEMF_B",
            "11": "BEMF_C", "12": "ISENSE", "13": "INLC", "14": "INLB", "15": "INLA",
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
